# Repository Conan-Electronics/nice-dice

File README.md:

# Nice Dice
Электронный кубик d6 на светодиодах.

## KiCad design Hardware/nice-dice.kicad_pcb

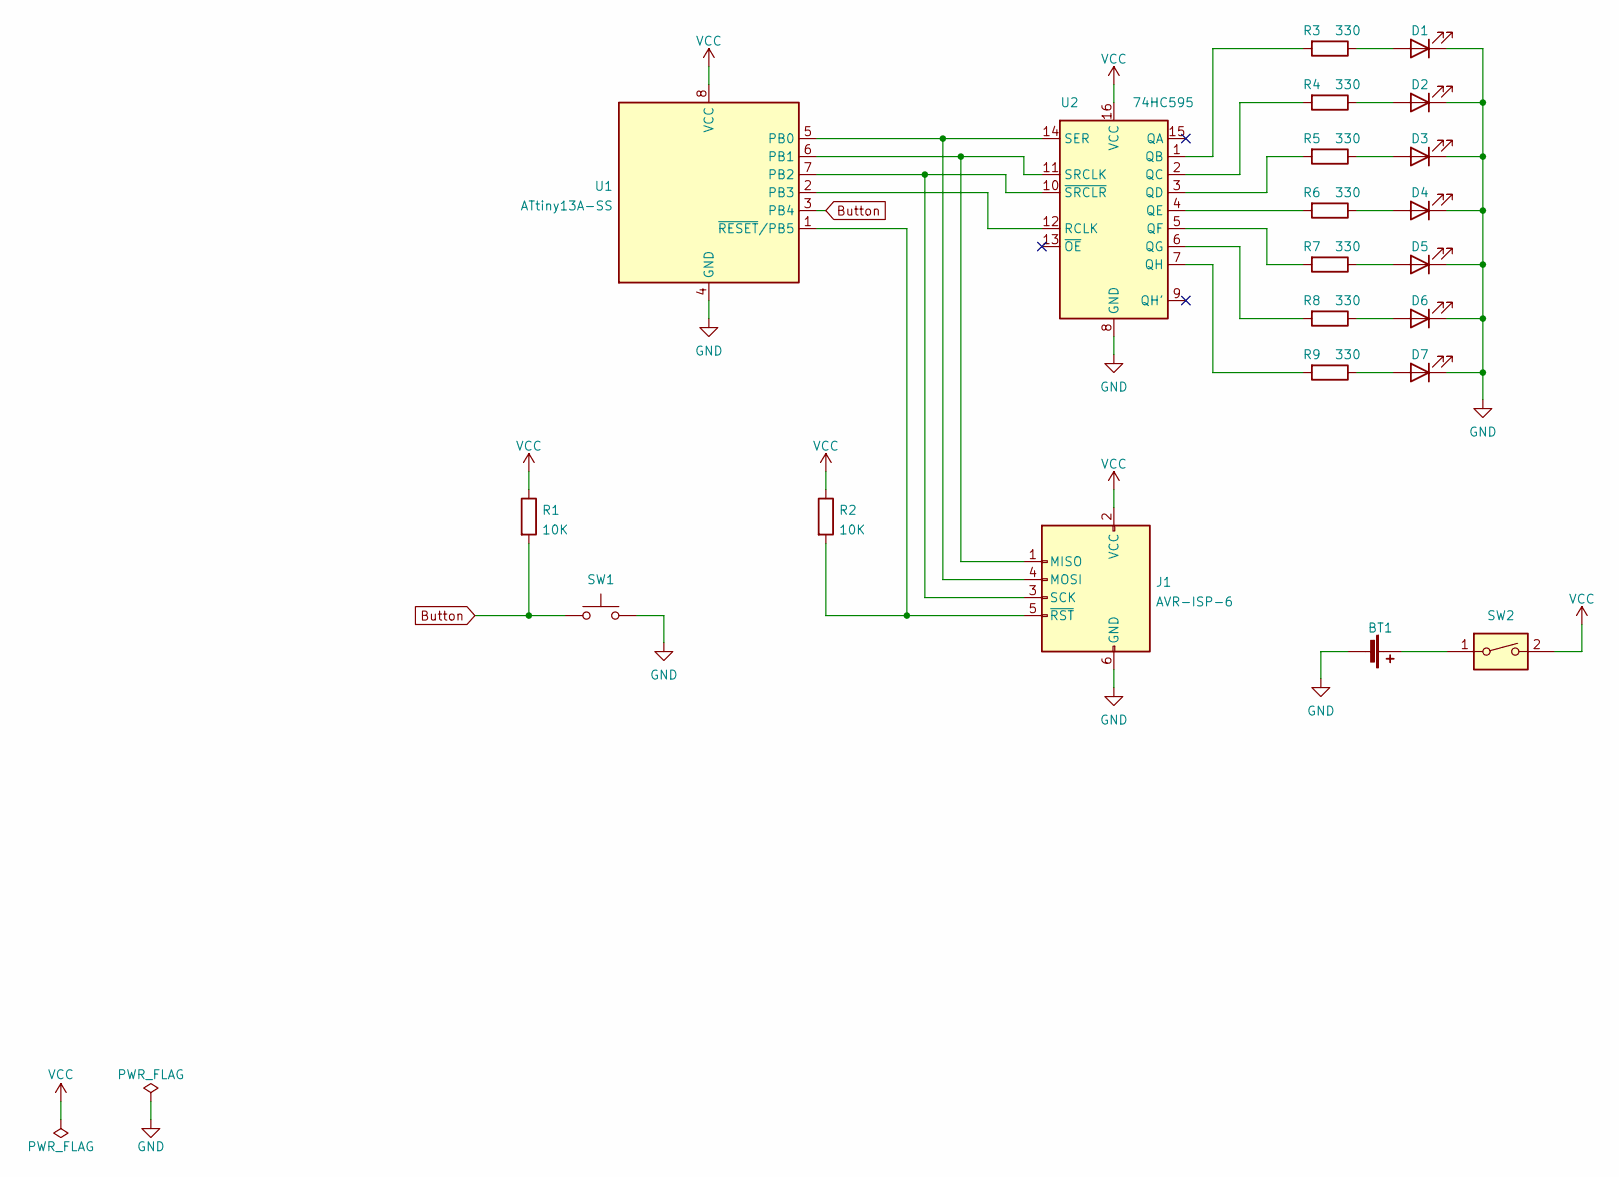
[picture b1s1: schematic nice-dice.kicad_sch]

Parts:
BT1: Battery_Cell; BatteryHolder_Keystone_3002_1x2032
D1, D2, D3, D4, D5, D6, D7: LED; LED_D3.0mm
J1: AVR-ISP-6; PinSocket_2x03_P2.54mm_Vertical
R1, R2: 10K; R_1206_3216Metric_Pad1.30x1.75mm_HandSolder
R3, R4, R5, R6, R7, R8, R9: 330; R_1206_3216Metric_Pad1.30x1.75mm_HandSolder
SW1: SW_Push; SW_Push_1P1T_NO_6x6mm_H9.5mm
SW2: SW_DIP_x01; SW_DIP_SPSTx01_Slide_Copal_CHS-01B_W7.62mm_P1.27mm
U1: ATtiny13A-SS; SOIC-8_3.9x4.9mm_P1.27mm
U2: 74HC595; SOIC-16_3.9x9.9mm_P1.27mm

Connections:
Button: R1.2, SW1.1, U1.3 (PB4)
GND: BT1.2 (-), D1.1 (K), D2.1 (K), D3.1 (K), D4.1 (K), D5.1 (K), D6.1 (K), D7.1 (K), J1.6 (GND), SW1.2, U1.4 (GND), U2.8 (GND)
unnamed: BT1.1 (+), SW2.1
unnamed: D1.2 (A), R3.1
unnamed: D2.2 (A), R4.1
unnamed: D3.2 (A), R5.1
unnamed: D4.2 (A), R6.1
unnamed: D5.2 (A), R7.1
unnamed: D6.2 (A), R8.1
unnamed: D7.2 (A), R9.1
unnamed: J1.1 (MISO), U1.6 (PB1), U2.11 (SRCLK)
unnamed: J1.3 (SCK), U1.7 (PB2), U2.10 (~SRCLR)
unnamed: J1.4 (MOSI), U1.5 (PB0), U2.14 (SER)
unnamed: J1.5 (~RST), R2.2, U1.1 (~RESET/PB5)
unnamed: R3.2, U2.1 (QB)
unnamed: R4.2, U2.2 (QC)
unnamed: R5.2, U2.3 (QD)
unnamed: R6.2, U2.4 (QE)
unnamed: R7.2, U2.5 (QF)
unnamed: R8.2, U2.6 (QG)
unnamed: R9.2, U2.7 (QH)
unnamed: U1.2 (PB3), U2.12 (RCLK)
VCC: J1.2 (VCC), R1.1, R2.1, SW2.2, U1.8 (VCC), U2.16 (VCC)

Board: 2 copper layers, 22 parts (7 on the bottom side), 23 nets, no tracks yet.

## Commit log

2021-09-10 Добавлен DIP вариант кубика
2021-09-10 Нарисована схема
2021-09-10 В схеме DIP версии прописаны все футпринты
2021-09-10 Исправлена кнопка
2021-09-10 Нарисован черновик платы DIP варианта
2021-09-10 Закончена разводка платы
2022-08-07 Переосмысление проекта
2022-08-07 Оформлена схема
2022-08-07 Начало работы над печатной платойплатой
2022-08-07 Добавлена прошивка
2022-08-09 Добавлен основной функционал
2022-08-09 Добавлена инициализация рандомайзера
2022-08-09 Изменены подключения OE и SRCLR
2022-08-09 Изменены подключения OE и SRCLR сдвигового регистра
2022-08-09 Добавлен футпринт на держатель для батарейки
2022-08-09 Добавлена библиотека с футпринтами
2022-08-09 Добавлена подтяжка выхода OE сдвигового регистра
2023-02-23 Отображение чисел приведено в соответствие с финальной платой
